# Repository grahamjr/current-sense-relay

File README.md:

# current-sense-relay
ISO micro relay, sourcing, current detect with open collector indicator

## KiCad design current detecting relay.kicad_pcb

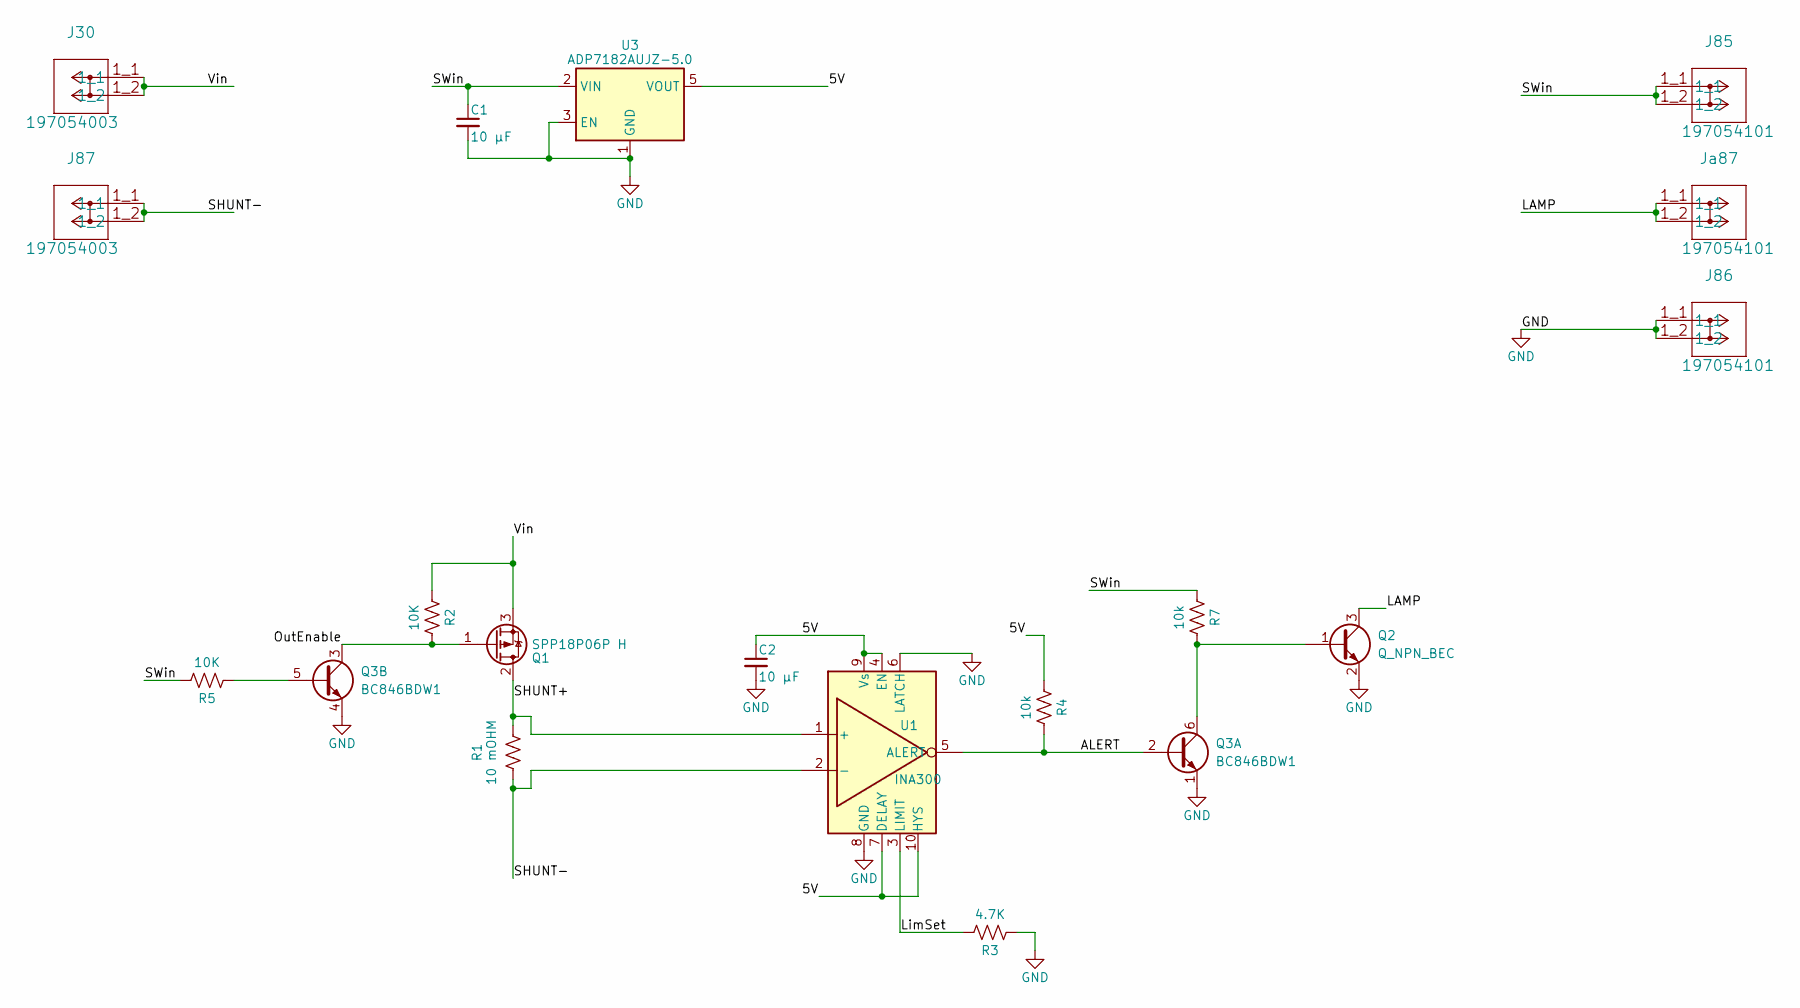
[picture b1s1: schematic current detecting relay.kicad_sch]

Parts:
C1, C2: 10 µF; C_0603_1608Metric
J30, J87: 197054003
J85, J86: 197054101
Ja87: 197054101
Q1: SPP18P06P H; TO-220-3_Vertical
Q2: Q_NPN_BEC; SOT-723
Q3: BC846BDW1; SOT-363_SC-70-6
R1: 10 mOHM; R_1206_3216Metric_Pad1.30x1.75mm_HandSolder; MFGPN PCS1206DR0100ET
R2, R5: 10K; R_0603_1608Metric
R3: 4.7K; R_0603_1608Metric
R4, R7: 10k; R_0603_1608Metric
U1: INA300; SON40P200X200X80-11N
U3: ADP7182AUJZ-5.0; TSOT-23-5

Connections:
/5V: C2.1, R4.1, U1.4 (EN), U1.7 (DELAY), U1.9 (Vs), U1.10 (HYS), U3.5 (VOUT)
/ALERT: Q3.2 (B1), R4.2, U1.5 (ALERT)
/LAMP: Ja87.1_1, Ja87.1_2, Q2.3 (C)
/LimSet: R3.2, U1.3 (LIMIT)
/OutEnable: Q1.1 (G), Q3.3 (C2), R2.2
/SHUNT+: Q1.2 (D), R1.1, U1.1 (+)
/SHUNT-: J87.1_1, J87.1_2, R1.2, U1.2 (-)
/SWin: C1.1, J85.1_1, J85.1_2, R5.2, R7.1, U3.2 (VIN)
/Vin: J30.1_1, J30.1_2, Q1.3 (S), R2.1
GND: C1.2, C2.2, J86.1_1, J86.1_2, Q2.2 (E), Q3.1 (E1), Q3.4 (E2), R3.1, U1.6 (LATCH), U1.8 (GND), U3.1 (GND), U3.3 (EN)
unnamed: Q2.1 (B), Q3.6 (C1), R7.2
unnamed: Q3.5 (B2), R5.1

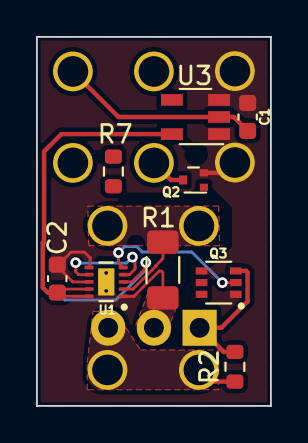
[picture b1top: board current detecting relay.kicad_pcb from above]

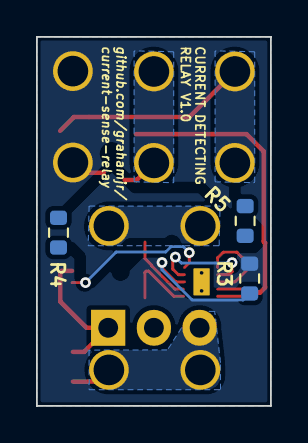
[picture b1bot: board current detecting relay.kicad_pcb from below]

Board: 2 copper layers, 13.0 x 20.5 mm, 18 parts (8 on the bottom side), 12 nets.

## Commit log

2026-02-16 init working example. Needs review
2026-02-16 Selected smaller transistors, layout tentative
2026-02-19 Worked on layout and cleaning up silk screen
2026-02-21 Upgraded to kicad V9

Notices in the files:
parts and their libraries:
Copyright 2016 Accelerated Designs. All rights reserved.
